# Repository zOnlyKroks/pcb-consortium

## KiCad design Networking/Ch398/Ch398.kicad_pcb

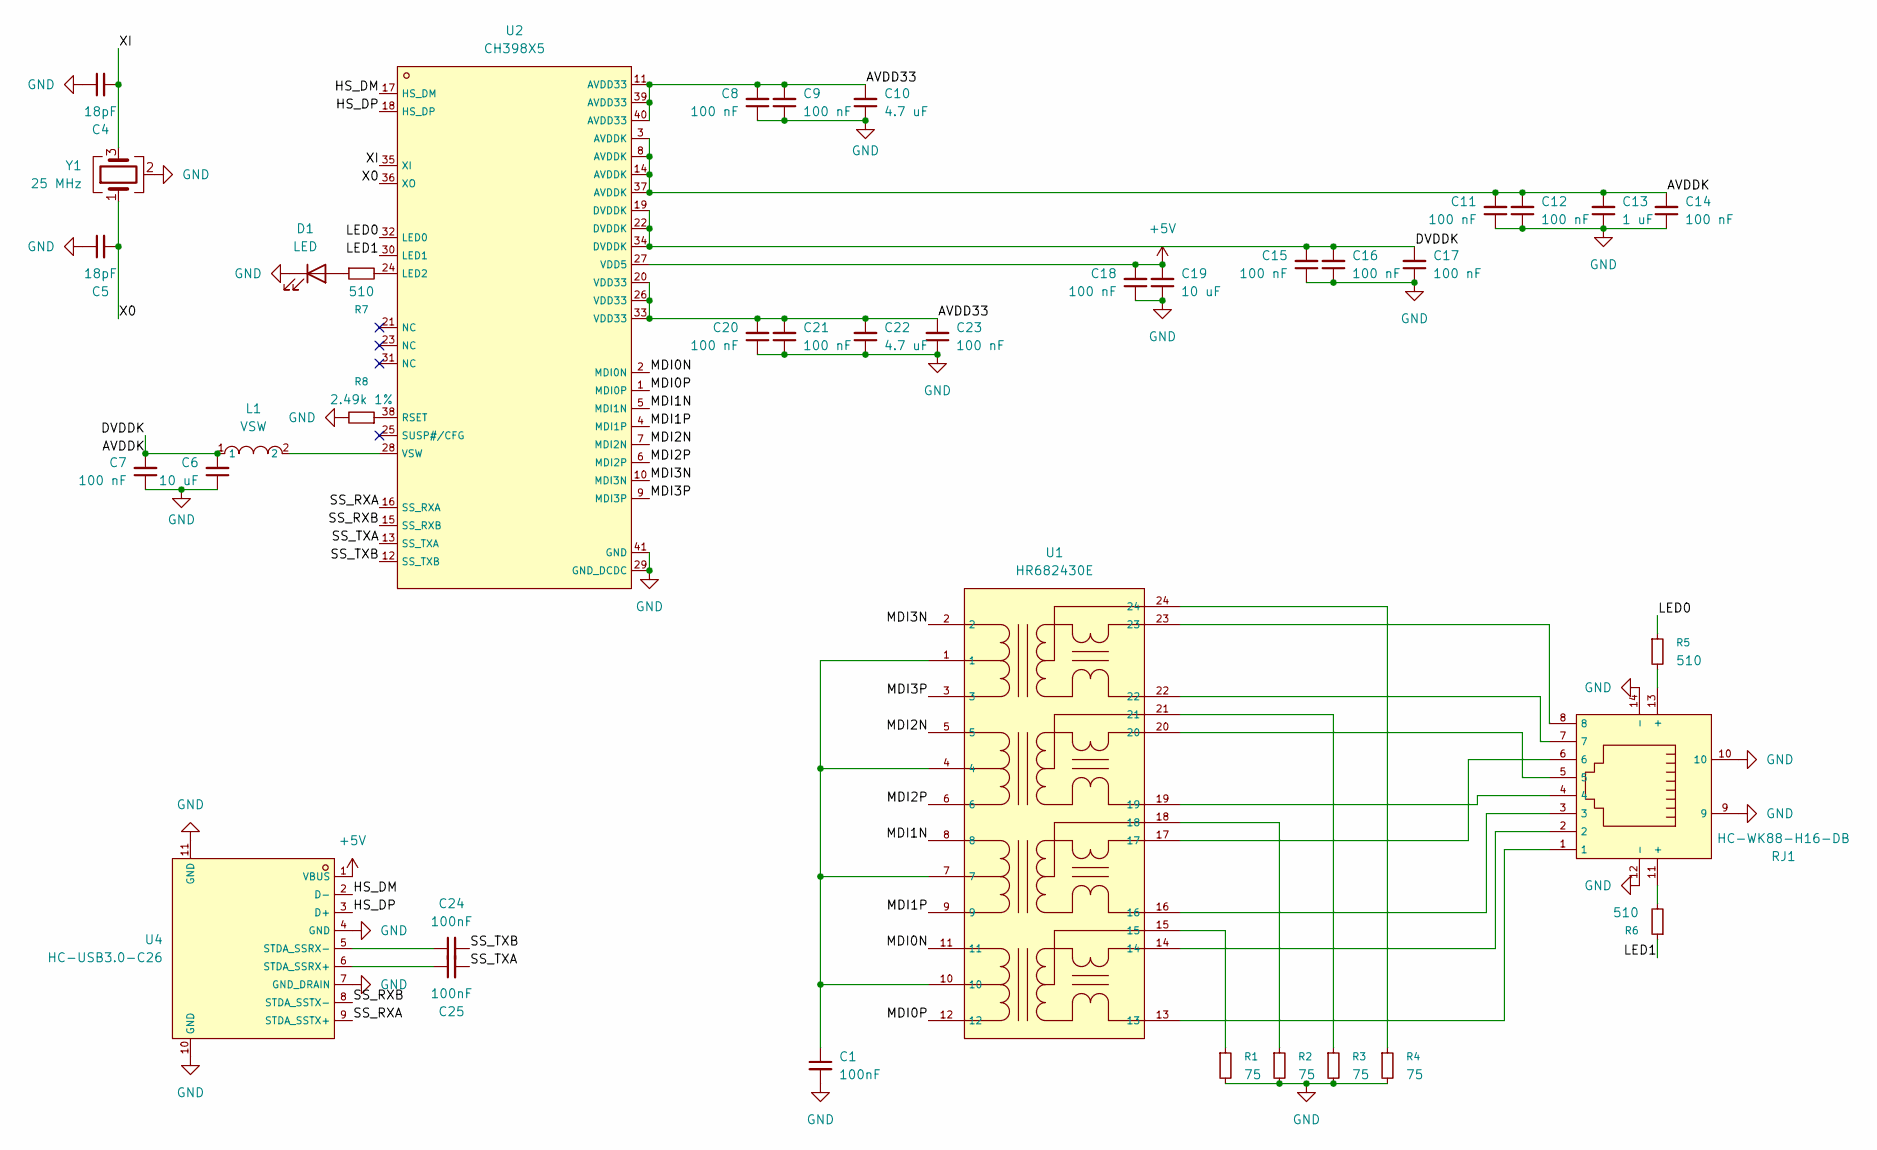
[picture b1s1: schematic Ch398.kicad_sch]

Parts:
C1, C24, C25: 100nF; C_0603_1608Metric
C4, C5: 18pF; C_0603_1608Metric
C6: 10 uF; C_0603_1608Metric
C7, C8, C9, C11, C12, C14, C15, C16, C17, C18, C20, C21, C23: 100 nF; C_0603_1608Metric
C10, C22: 4.7 uF; C_0805_2012Metric
C13: 1 uF; C_0603_1608Metric
C19: 10 uF; C_0805_2012Metric
D1: LED; LED_0805_2012Metric
L1: VSW; C47327201_IND-SMD_L7_7-W6_6_APS0630; LCSC C47327201
R1, R2, R3, R4: 75; R_0603_1608Metric
R5, R6, R7: 510; R_0603_1608Metric
R8: 2.49k 1%; R_0603_1608Metric
RJ1: HC-WK88-H16-DB; C7501824_RJ45-TH_HC-WK88-H16-DB; LCSC C7501824
U1: HR682430E; C3020103_SMD-24_L15_1-W7_1-P1_00-LS10_0-BL; LCSC C3020103
U2: CH398X5; C55013891_VQFN-40_L5_0-W5_0-P0_40-TL-EP3_5; LCSC C55013891
U4: HC-USB3.0-C26; C7501854_USB-3_0-A-SMD_HC-USB3_0-C26; LCSC C7501854
Y1: 25 MHz; Crystal_SMD_3225-4Pin_3.2x2.5mm

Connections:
+5V: C18.2, C19.2, U2.27 (VDD5), U4.1 (VBUS)
/AVDD33: C8.2, C9.2, C10.2, C20.2, C21.2, C22.2, C23.2, U2.11 (AVDD33), U2.20 (VDD33), U2.26 (VDD33), U2.33 (VDD33), U2.39 (AVDD33), U2.40 (AVDD33)
/AVDDK: C6.2, C7.2, C11.2, C12.2, C13.2, C14.2, C15.2, C16.2, C17.2, L1.1, U2.3 (AVDDK), U2.8 (AVDDK), U2.14 (AVDDK), U2.19 (DVDDK), U2.22 (DVDDK), U2.34 (DVDDK), U2.37 (AVDDK)
/HS_DM: U2.17 (HS_DM), U4.2 (D-)
/HS_DP: U2.18 (HS_DP), U4.3 (D+)
/LED0: R5.1, U2.32 (LED0)
/LED1: R6.1, U2.30 (LED1)
/MDI0N: U1.11, U2.2 (MDI0N)
/MDI0P: U1.12, U2.1 (MDI0P)
/MDI1N: U1.8, U2.5 (MDI1N)
/MDI1P: U1.9, U2.4 (MDI1P)
/MDI2N: U1.5, U2.7 (MDI2N)
/MDI2P: U1.6, U2.6 (MDI2P)
/MDI3N: U1.2, U2.10 (MDI3N)
/MDI3P: U1.3, U2.9 (MDI3P)
/SS_RXA: U2.16 (SS_RXA), U4.9 (STDA_SSTX+)
/SS_RXB: U2.15 (SS_RXB), U4.8 (STDA_SSTX-)
/SS_TXA: C25.2, U2.13 (SS_TXA)
/SS_TXB: C24.2, U2.12 (SS_TXB)
/X0: C5.2, U2.36 (XO), Y1.1
/XI: C4.2, U2.35 (XI), Y1.3
GND: C1.2, C4.1, C5.1, C6.1, C7.1, C8.1, C9.1, C10.1, C11.1, C12.1, C13.1, C14.1, C15.1, C16.1, C17.1, C18.1, C19.1, C20.1, C21.1, C22.1, C23.1, D1.1 (K), R1.2, R2.2, R3.2, R4.2, R8.2, RJ1.9, RJ1.10, RJ1.12 (-), RJ1.14 (-), U2.29 (GND_DCDC), U2.41 (GND), U4.4 (GND), U4.7 (GND_DRAIN), U4.10 (GND), U4.11 (GND), Y1.2 (G), Y1.4 (G)
unnamed: C1.1, U1.1, U1.4, U1.7, U1.10
unnamed: D1.2 (A), R7.1
unnamed: R1.1, U1.15
unnamed: R2.1, U1.18
unnamed: R3.1, U1.21
unnamed: R4.1, U1.24
unnamed: R5.2, RJ1.13 (+)
unnamed: R6.2, RJ1.11 (+)
unnamed: RJ1.1, U1.13
unnamed: RJ1.2, U1.14
unnamed: RJ1.3, U1.16
unnamed: RJ1.4, U1.19
unnamed: RJ1.5, U1.20
unnamed: RJ1.6, U1.17
unnamed: RJ1.7, U1.22
unnamed: RJ1.8, U1.23
unnamed: R7.2, U2.24 (LED2)
unnamed: R8.1, U2.38 (RSET)
unnamed: L1.2, U2.28 (VSW)
unnamed: C25.1, U4.6 (STDA_SSRX+)
unnamed: C24.1, U4.5 (STDA_SSRX-)

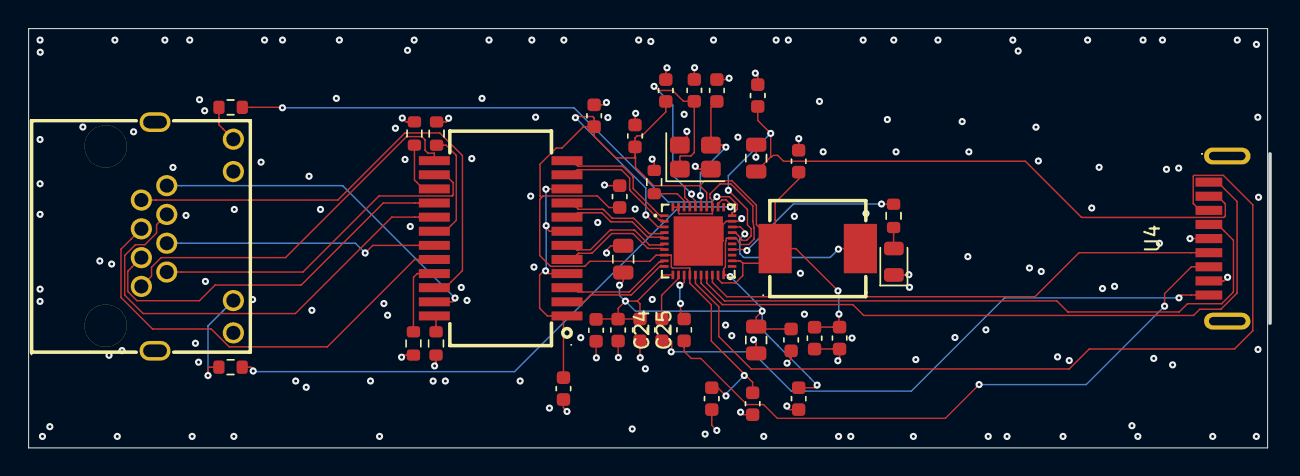
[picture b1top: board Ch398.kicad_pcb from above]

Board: 4 copper layers, 87.8 x 29.7 mm, 38 parts (0 on the bottom side), 43 nets.

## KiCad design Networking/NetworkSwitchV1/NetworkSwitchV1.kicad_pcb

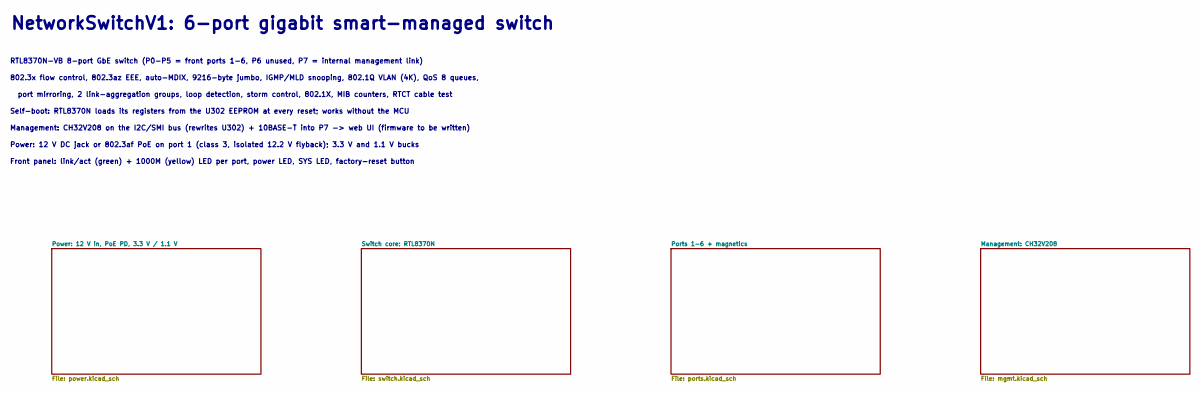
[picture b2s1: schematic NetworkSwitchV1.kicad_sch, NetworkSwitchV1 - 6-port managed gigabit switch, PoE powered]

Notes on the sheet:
Self-boot: RTL8370N loads its registers from the U302 EEPROM at every reset; works without the MCU
NetworkSwitchV1: 6-port gigabit smart-managed switch
802.3x flow control, 802.3az EEE, auto-MDIX, 9216-byte jumbo, IGMP/MLD snooping, 802.1Q VLAN (4K), QoS 8 queues,
Front panel: link/act (green) + 1000M (yellow) LED per port, power LED, SYS LED, factory-reset button
Power: 12 V DC jack or 802.3af PoE on port 1 (class 3, isolated 12.2 V flyback); 3.3 V and 1.1 V bucks
RTL8370N-VB 8-port GbE switch (P0-P5 = front ports 1-6, P6 unused, P7 = internal management link)
Management: CH32V208 on the I2C/SMI bus (rewrites U302) + 10BASE-T into P7 -> web UI (firmware to be written)
port mirroring, 2 link-aggregation groups, loop detection, storm control, 802.1X, MIB counters, RTCT cable test

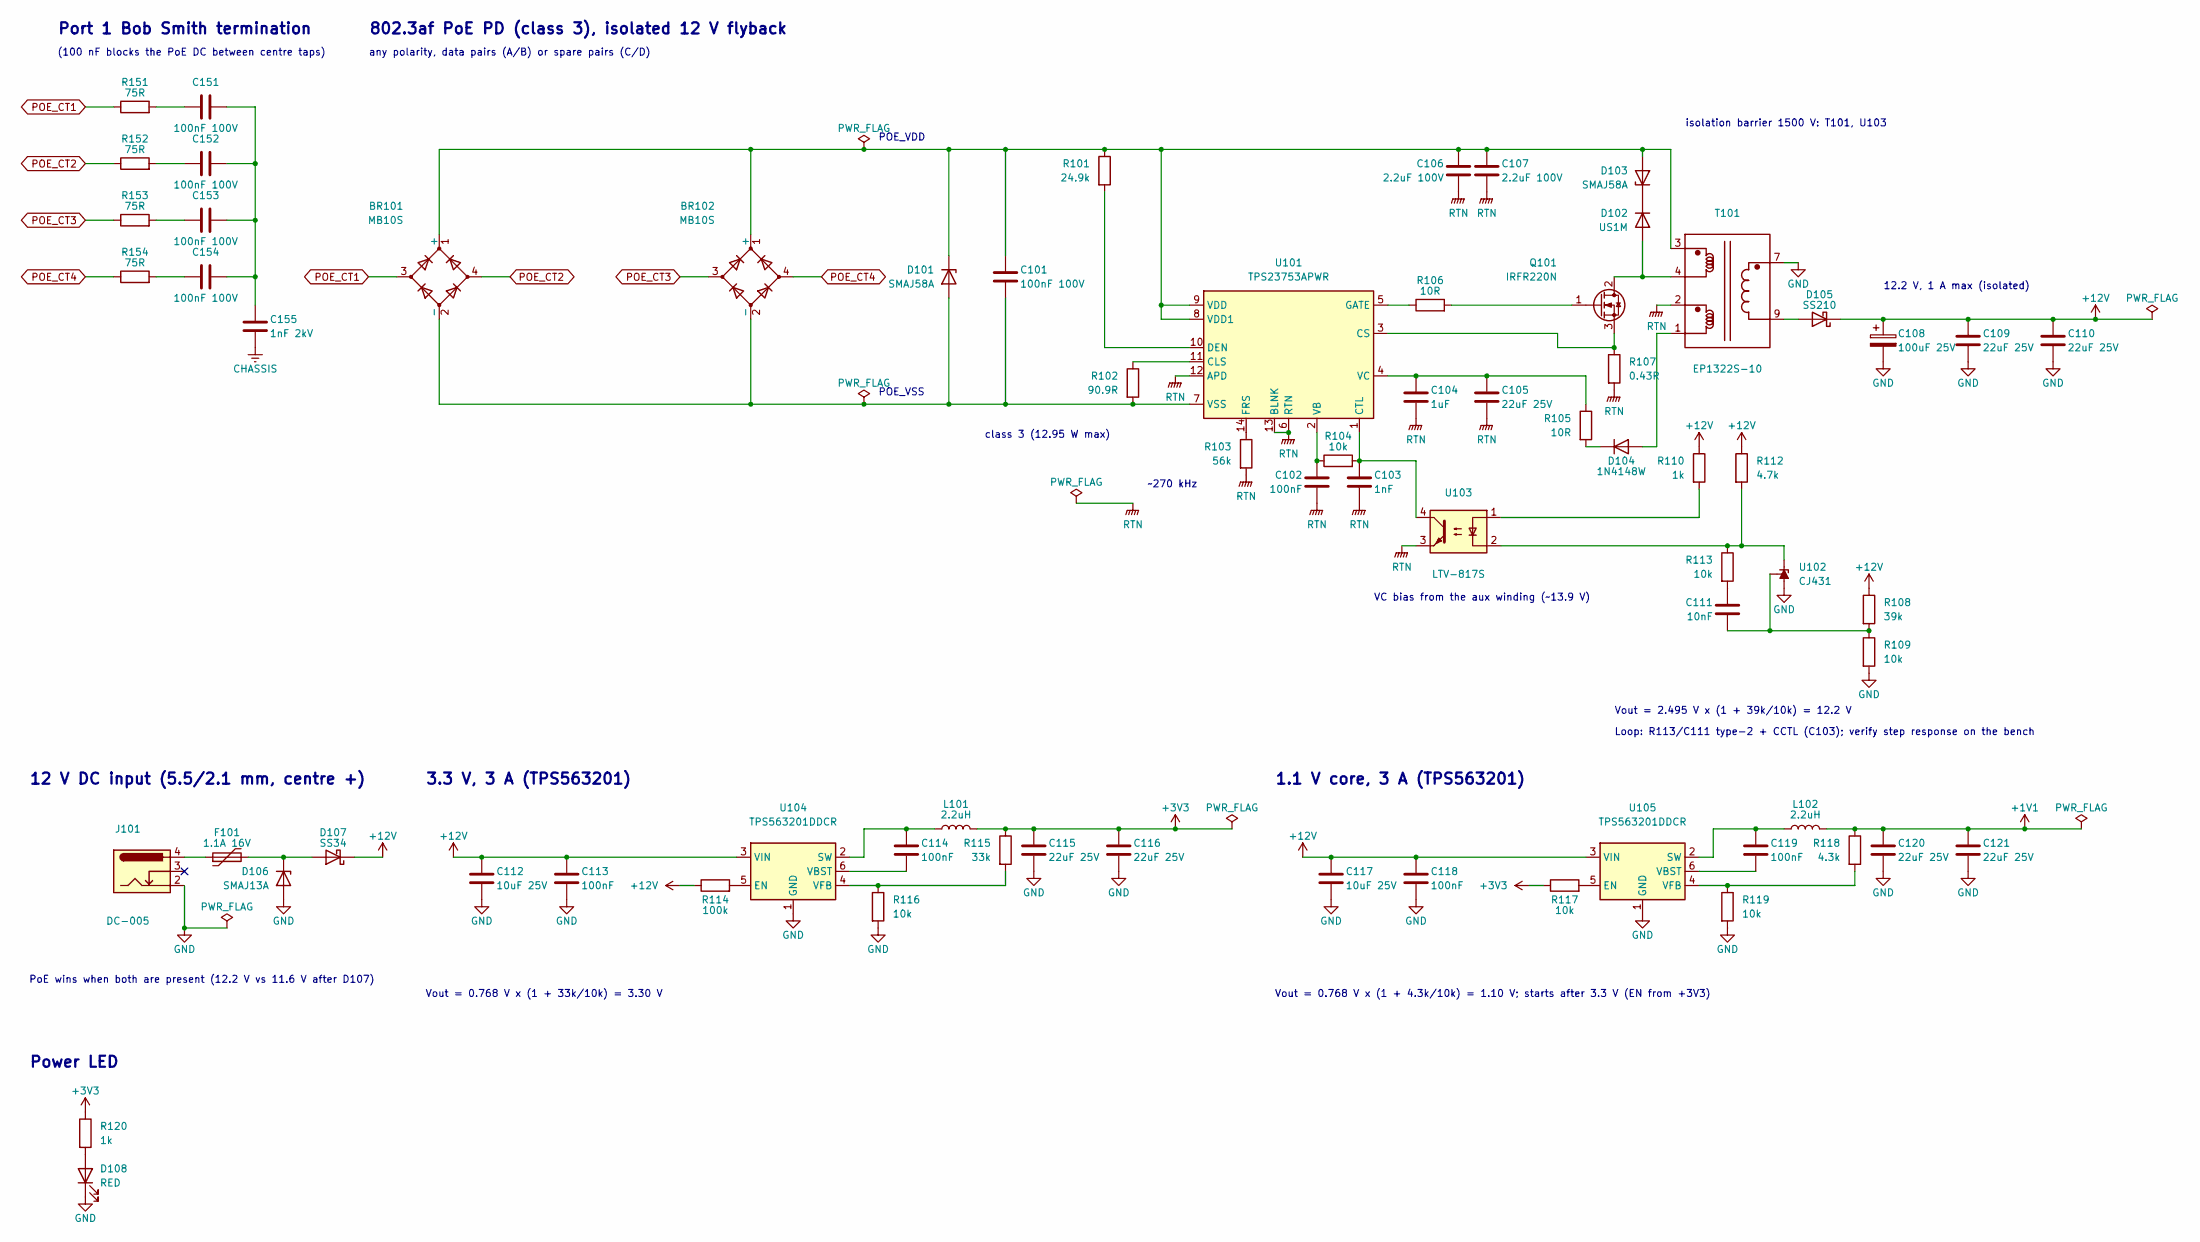
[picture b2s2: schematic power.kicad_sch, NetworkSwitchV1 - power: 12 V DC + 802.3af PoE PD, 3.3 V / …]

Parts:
BR101, BR102: MB10S; MBS_L4.7-W3.8-P2.40-LS7.0-TL; LCSC Part # C2488
C101, C151, C152, C153, C154: 100nF 100V; C_0805_2012Metric; LCSC Part # C28233
C102, C113, C114, C118, C119: 100nF; C_0603_1608Metric; LCSC Part # C14663
C103: 1nF; C_0603_1608Metric; LCSC Part # C1588
C104: 1uF; C_0603_1608Metric; LCSC Part # C15849
C105, C109, C110, C115, C116, C120, C121: 22uF 25V; C_0805_2012Metric; LCSC Part # C45783
C106, C107: 2.2uF 100V; C_1210_3225Metric; LCSC Part # C55151
C108: 100uF 25V; CP_Elec_6.3x7.7; LCSC Part # C970685
C111: 10nF; C_0603_1608Metric; LCSC Part # C57112
C112, C117: 10uF 25V; C_0805_2012Metric; LCSC Part # C15850
C155: 1nF 2kV; C_1206_3216Metric; LCSC Part # C9196
D101, D103: SMAJ58A; D_SMA; LCSC Part # C123816
D102: US1M; D_SMA; LCSC Part # C412437
D104: 1N4148W; D_SOD-123; LCSC Part # C81598
D105: SS210; D_SMA; LCSC Part # C14996
D106: SMAJ13A; D_SMA; LCSC Part # C10764
D107: SS34; D_SMA; LCSC Part # C8678
D108: RED; LED_0603_1608Metric; LCSC Part # C2286
F101: 1.1A 16V; Fuse_1206_3216Metric; LCSC Part # C7542961
J101: DC-005; DC-IN-TH_DC-005-5.5-2.0; LCSC Part # C16214
L101, L102: 2.2uH; IND-SMD_L4.0-W4.0_FNR40XXS; LCSC Part # C167869
Q101: IRFR220N; TO-252-2_L6.6-W6.1-P4.57-LS9.9-BR-CW; Rating 200 V 8 A; LCSC Part # C22365390
R101: 24.9k; R_0603_1608Metric; LCSC Part # C25962
R102: 90.9R; R_0603_1608Metric; LCSC Part # C23130
R103: 56k; R_0603_1608Metric; LCSC Part # C23206
R104, R109, R113, R116, R117, R119: 10k; R_0603_1608Metric; LCSC Part # C25804
R105, R106: 10R; R_0603_1608Metric; LCSC Part # C22859
R107: 0.43R; R_1206_3216Metric; LCSC Part # C24965
R108: 39k; R_0603_1608Metric; LCSC Part # C23153
R110, R120: 1k; R_0603_1608Metric; LCSC Part # C21190
R112: 4.7k; R_0603_1608Metric; LCSC Part # C23162
R114: 100k; R_0603_1608Metric; LCSC Part # C25803
R115: 33k; R_0603_1608Metric; LCSC Part # C4216
R118: 4.3k; R_0603_1608Metric; LCSC Part # C23159
R151, R152, R153, R154: 75R; R_0603_1608Metric; LCSC Part # C4275
T101: EP1322S-10; XFMR-SMD_EP1322S-10; LCSC Part # C37328796
U101: TPS23753APWR; TSSOP-14_L5.0-W4.4-P0.65-LS6.4-BL; LCSC Part # C92115
U102: CJ431; SOT-23-3_L2.9-W1.6-P1.90-LS2.8-BR; LCSC Part # C3113
U103: LTV-817S; OPTO-SMD-4_L4.6-W6.5-P2.54-LS10.3-BL; LCSC Part # C109227
U104, U105: TPS563201DDCR; TSOT-23-6; LCSC Part # C116592

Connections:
+1V1: C120.1, C121.1, L102.2, R118.1; also elsewhere on the board
+3V3: C115.1, C116.1, L101.2, R115.1, R117.1, R120.1; also elsewhere on the board
+12V: C108.1, C109.1, C110.1, C112.1, C113.1, C117.1, C118.1, D105.1 (K), D107.1 (K), R108.1, R110.1, R112.1, R114.1, U104.3 (VIN), U105.3 (VIN)
CHASSIS: C155.2; also elsewhere on the board
GND: C108.2, C109.2, C110.2, C112.2, C113.2, C115.2, C116.2, C117.2, C118.2, C120.2, C121.2, D106.2 (A), D108.1 (K), J101.2, R109.2, R116.2, R119.2, T101.7, T101.8, U102.3 (A), U104.1 (GND), U105.1 (GND); also elsewhere on the board
unnamed: BR101.1 (+), BR102.1 (+), C101.1, C106.1, C107.1, D101.1 (K), D103.2 (A), R101.1, T101.3, U101.8 (VDD1), U101.9 (VDD)
unnamed: BR101.2 (-), BR102.2 (-), C101.2, D101.2 (A), R102.2, U101.7 (VSS)
unnamed: C111.1, R113.2
unnamed: C151.1, R151.2
unnamed: C151.2, C152.2, C153.2, C154.2, C155.1
unnamed: C152.1, R152.2
unnamed: C153.1, R153.2
unnamed: C154.1, R154.2
unnamed: D102.2 (A), Q101.2 (D), T101.4
unnamed: D102.1 (K), D103.1 (K)
unnamed: D104.2 (A), T101.1
unnamed: D104.1 (K), R105.2
unnamed: D105.2 (A), T101.9, T101.10
unnamed: D106.1 (K), D107.2 (A), F101.2
unnamed: D108.2 (A), R120.2
unnamed: F101.1, J101.4
unnamed: Q101.1 (G), R106.2
unnamed: Q101.3 (S), R107.1, U101.3 (CS)
unnamed: R110.2, U103.1
unnamed: R102.1, U101.11 (CLS)
unnamed: C103.1, R104.2, U101.1 (CTL), U103.4
unnamed: R101.2, U101.10 (DEN)
unnamed: R103.1, U101.14 (FRS)
unnamed: R106.1, U101.5 (GATE)
unnamed: C102.1, R104.1, U101.2 (VB)
unnamed: C104.1, C105.1, R105.1, U101.4 (VC)
unnamed: R112.2, R113.1, U102.2 (K), U103.2
unnamed: C111.2, R108.2, R109.1, U102.1 (REF)
unnamed: R114.2, U104.5 (EN)
unnamed: C114.1, L101.1, U104.2 (SW)
unnamed: C114.2, U104.6 (VBST)
unnamed: R115.2, R116.1, U104.4 (VFB)
unnamed: R117.2, U105.5 (EN)
unnamed: C119.1, L102.1, U105.2 (SW)
unnamed: C119.2, U105.6 (VBST)
unnamed: R118.2, R119.1, U105.4 (VFB)
POE_CT1: BR101.3, R151.1; also elsewhere on the board
POE_CT2: BR101.4, R152.1; also elsewhere on the board
POE_CT3: BR102.3, R153.1; also elsewhere on the board
POE_CT4: BR102.4, R154.1; also elsewhere on the board
RTN: C102.2, C103.2, C104.2, C105.2, C106.2, C107.2, R103.2, R107.2, T101.2, U101.6 (RTN), U101.12 (APD), U101.13 (BLNK), U103.3

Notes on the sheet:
any polarity, data pairs (A/B) or spare pairs (C/D)
3.3 V, 3 A (TPS563201)
Vout = 2.495 V x (1 + 39k/10k) = 12.2 V
~270 kHz
class 3 (12.95 W max)
Port 1 Bob Smith termination
Loop: R113/C111 type-2 + CCTL (C103); verify step response on the bench
802.3af PoE PD (class 3), isolated 12 V flyback
POE_VDD
VC bias from the aux winding (~13.9 V)
1.1 V core, 3 A (TPS563201)
12.2 V, 1 A max (isolated)
Vout = 0.768 V x (1 + 33k/10k) = 3.30 V
POE_VSS
Vout = 0.768 V x (1 + 4.3k/10k) = 1.10 V; starts after 3.3 V (EN from +3V3)
isolation barrier 1500 V: T101, U103
(100 nF blocks the PoE DC between centre taps)
Power LED
12 V DC input (5.5/2.1 mm, centre +)
PoE wins when both are present (12.2 V vs 11.6 V after D107)

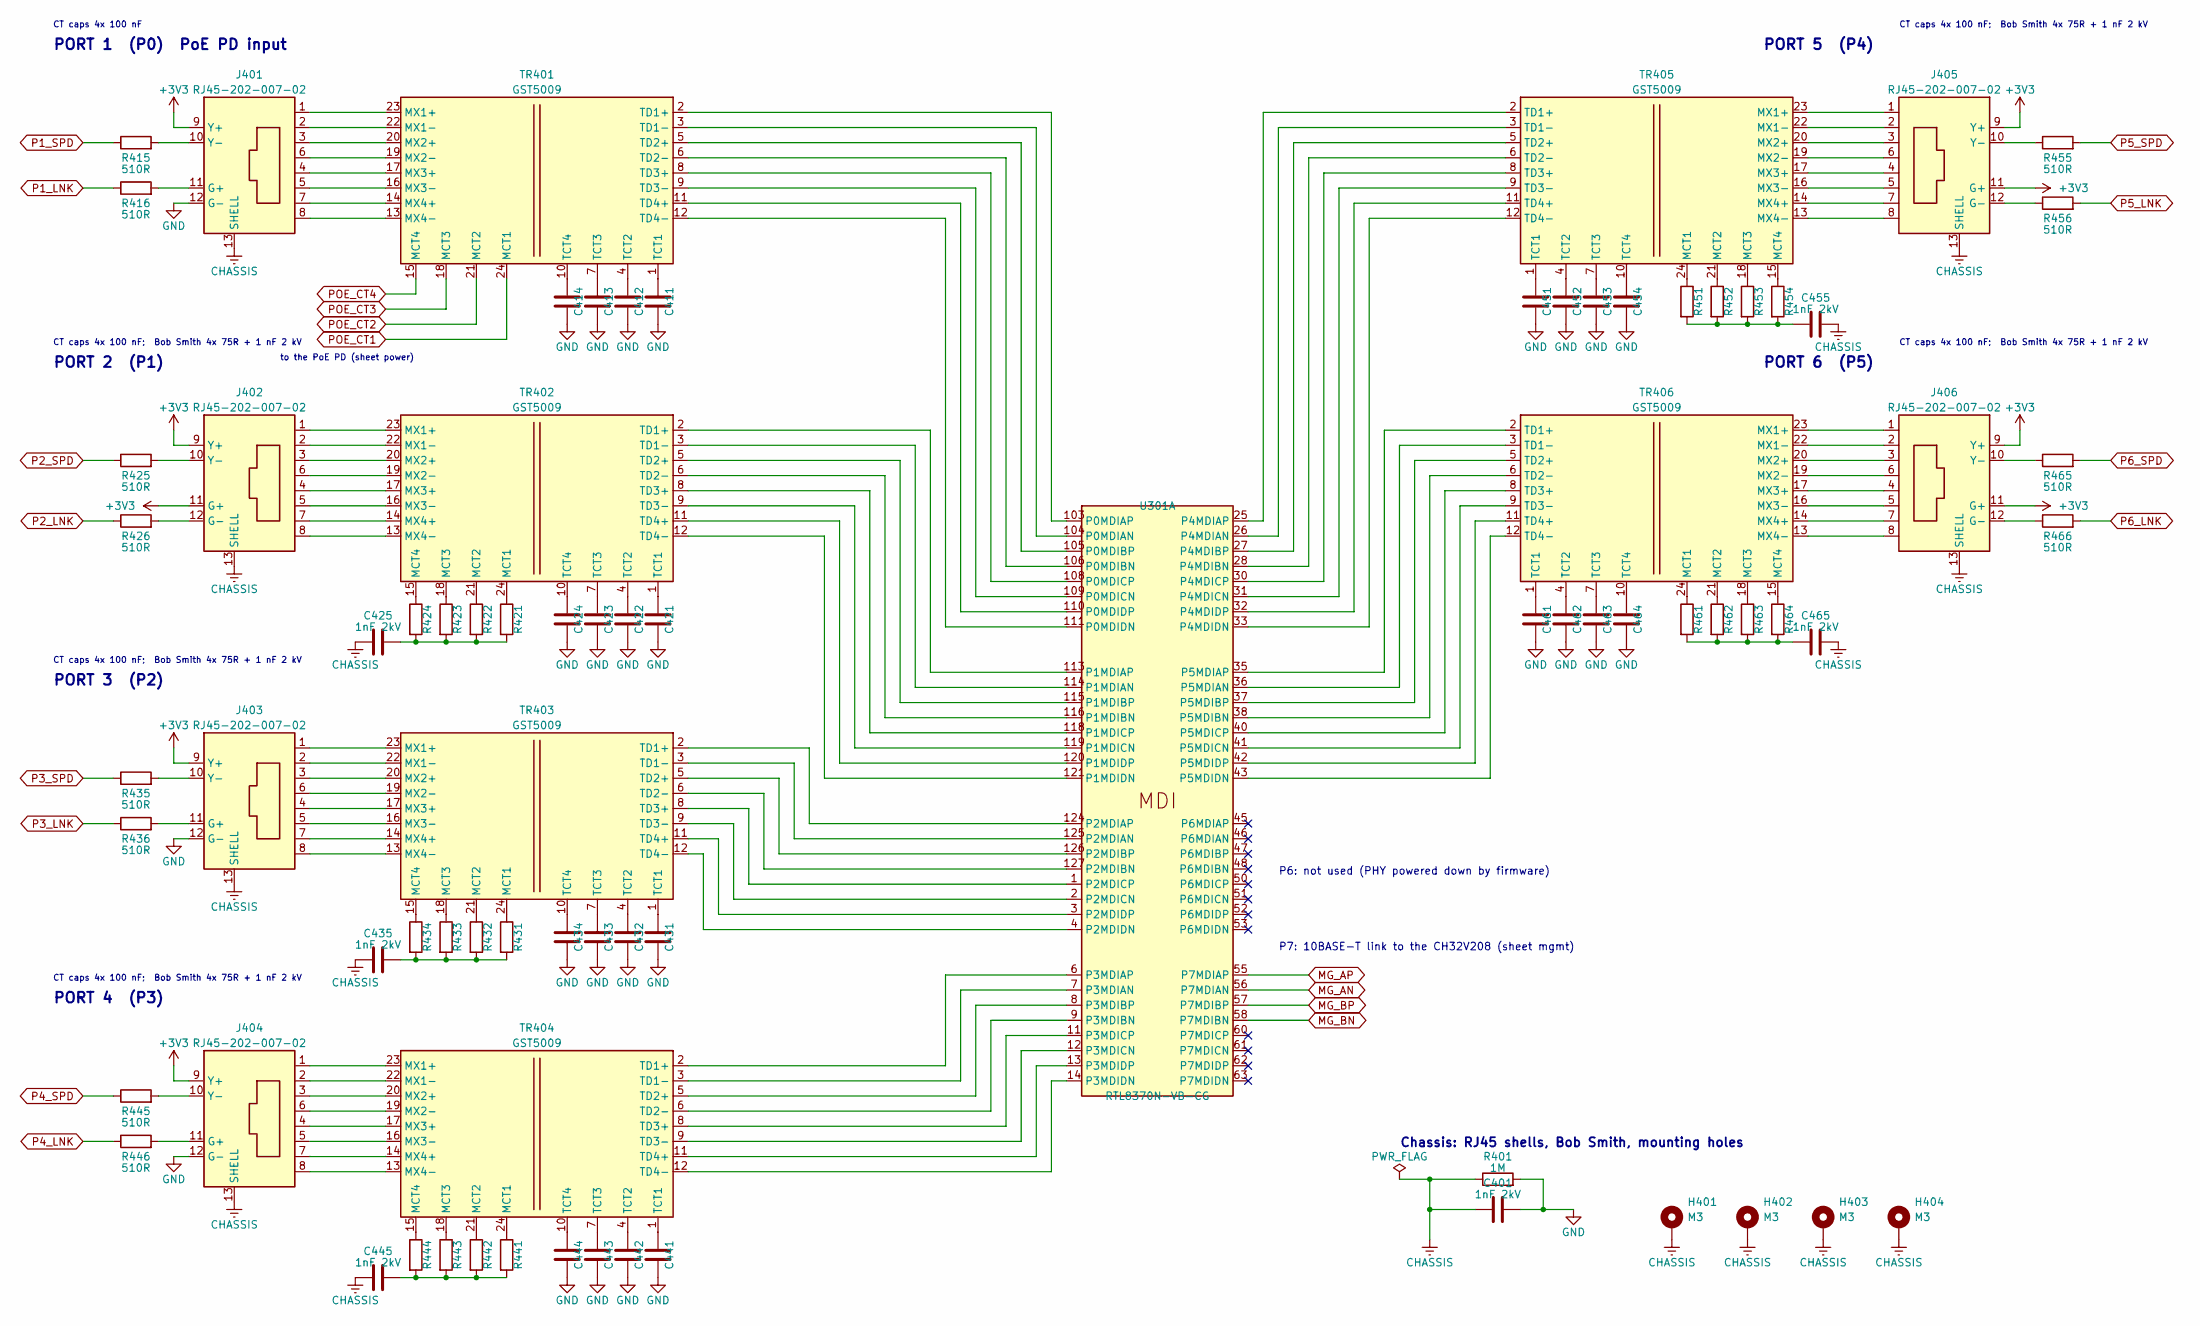
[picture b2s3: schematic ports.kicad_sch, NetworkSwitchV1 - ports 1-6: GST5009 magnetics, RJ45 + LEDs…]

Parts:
C401, C425, C435, C445, C455, C465: 1nF 2kV; C_1206_3216Metric; LCSC Part # C9196
C411, C412, C413, C414, C421, C422, C423, C424, C431, C432, C433, C434, C441, C442, C443, C444, C451, C452, C453, C454, C461, C462, C463, C464: 100nF; C_0603_1608Metric; LCSC Part # C14663
H401, H402, H403, H404: M3; MountingHole_3.2mm_M3_Pad_Via
J401, J402, J403, J404, J405, J406: RJ45-202-007-02; RJ45-TH_RJ45-202-007-02; LCSC Part # C7421418
R401: 1M; R_0603_1608Metric; LCSC Part # C22935
R415, R416, R425, R426, R435, R436, R445, R446, R455, R456, R465, R466: 510R; R_0603_1608Metric; LCSC Part # C23193
R421, R422, R423, R424, R431, R432, R433, R434, R441, R442, R443, R444, R451, R452, R453, R454, R461, R462, R463, R464: 75R; R_0603_1608Metric; LCSC Part # C4275
TR401, TR402, TR403, TR404, TR405, TR406: GST5009; XFMR-SMD_24P-L15.1-W7.1-P1.00-LS9.7-BL; LCSC Part # C55213474
U301: RTL8370N-VB-CG; LQFP-128_L20.0-W14.0-P0.50-BL-EP7.0; LCSC Part # C2803243

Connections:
+3V3: J401.9 (Y+), J402.9 (Y+), J402.11 (G+), J403.9 (Y+), J404.9 (Y+), J405.9 (Y+), J405.11 (G+), J406.9 (Y+), J406.11 (G+); also elsewhere on the board
CHASSIS: C401.1, C425.1, C435.1, C445.1, C455.2, C465.2, H401.1 (1_1), H402.1 (1_1), H403.1 (1_1), H404.1 (1_1), J401.13 (SHELL), J402.13 (SHELL), J403.13 (SHELL), J404.13 (SHELL), J405.13 (SHELL), J406.13 (SHELL), R401.1; also elsewhere on the board
GND: C401.2, C411.2, C412.2, C413.2, C414.2, C421.2, C422.2, C423.2, C424.2, C431.2, C432.2, C433.2, C434.2, C441.2, C442.2, C443.2, C444.2, C451.2, C452.2, C453.2, C454.2, C461.2, C462.2, C463.2, C464.2, J401.12 (G-), J403.12 (G-), J404.12 (G-), R401.2; also elsewhere on the board
MG_AN: U301.56 (P7MDIAN); also elsewhere on the board
MG_AP: U301.55 (P7MDIAP); also elsewhere on the board
MG_BN: U301.58 (P7MDIBN); also elsewhere on the board
MG_BP: U301.57 (P7MDIBP); also elsewhere on the board
unnamed: C425.2, R421.2, R422.2, R423.2, R424.2
unnamed: C435.2, R431.2, R432.2, R433.2, R434.2
unnamed: C445.2, R441.2, R442.2, R443.2, R444.2
unnamed: C455.1, R451.2, R452.2, R453.2, R454.2
unnamed: C465.1, R461.2, R462.2, R463.2, R464.2
unnamed: J401.11 (G+), R416.2
unnamed: J401.10 (Y-), R415.2
unnamed: J402.12 (G-), R426.2
unnamed: J402.10 (Y-), R425.2
unnamed: J403.11 (G+), R436.2
unnamed: J403.10 (Y-), R435.2
unnamed: J404.11 (G+), R446.2
unnamed: J404.10 (Y-), R445.2
unnamed: J405.12 (G-), R456.1
unnamed: J405.10 (Y-), R455.1
unnamed: J406.12 (G-), R466.1
unnamed: J406.10 (Y-), R465.1
unnamed: J401.1, TR401.23 (MX1+)
unnamed: J401.2, TR401.22 (MX1-)
unnamed: J401.3, TR401.20 (MX2+)
unnamed: J401.6, TR401.19 (MX2-)
unnamed: J401.4, TR401.17 (MX3+)
unnamed: J401.5, TR401.16 (MX3-)
unnamed: J401.7, TR401.14 (MX4+)
unnamed: J401.8, TR401.13 (MX4-)
unnamed: C411.1, TR401.1 (TCT1)
unnamed: C412.1, TR401.4 (TCT2)
unnamed: C413.1, TR401.7 (TCT3)
unnamed: C414.1, TR401.10 (TCT4)
unnamed: TR401.2 (TD1+), U301.103 (P0MDIAP)
unnamed: TR401.3 (TD1-), U301.104 (P0MDIAN)
unnamed: TR401.5 (TD2+), U301.105 (P0MDIBP)
unnamed: TR401.6 (TD2-), U301.106 (P0MDIBN)
unnamed: TR401.8 (TD3+), U301.108 (P0MDICP)
unnamed: TR401.9 (TD3-), U301.109 (P0MDICN)
unnamed: TR401.11 (TD4+), U301.110 (P0MDIDP)
unnamed: TR401.12 (TD4-), U301.111 (P0MDIDN)
unnamed: R421.1, TR402.24 (MCT1)
unnamed: R422.1, TR402.21 (MCT2)
unnamed: R423.1, TR402.18 (MCT3)
unnamed: R424.1, TR402.15 (MCT4)
unnamed: J402.1, TR402.23 (MX1+)
unnamed: J402.2, TR402.22 (MX1-)
unnamed: J402.3, TR402.20 (MX2+)
unnamed: J402.6, TR402.19 (MX2-)
unnamed: J402.4, TR402.17 (MX3+)
unnamed: J402.5, TR402.16 (MX3-)
unnamed: J402.7, TR402.14 (MX4+)
unnamed: J402.8, TR402.13 (MX4-)
unnamed: C421.1, TR402.1 (TCT1)
unnamed: C422.1, TR402.4 (TCT2)
unnamed: C423.1, TR402.7 (TCT3)
unnamed: C424.1, TR402.10 (TCT4)
unnamed: TR402.2 (TD1+), U301.113 (P1MDIAP)
unnamed: TR402.3 (TD1-), U301.114 (P1MDIAN)
unnamed: TR402.5 (TD2+), U301.115 (P1MDIBP)
unnamed: TR402.6 (TD2-), U301.116 (P1MDIBN)
unnamed: TR402.8 (TD3+), U301.118 (P1MDICP)
unnamed: TR402.9 (TD3-), U301.119 (P1MDICN)
unnamed: TR402.11 (TD4+), U301.120 (P1MDIDP)
unnamed: TR402.12 (TD4-), U301.121 (P1MDIDN)
unnamed: R431.1, TR403.24 (MCT1)
unnamed: R432.1, TR403.21 (MCT2)
unnamed: R433.1, TR403.18 (MCT3)
unnamed: R434.1, TR403.15 (MCT4)
unnamed: J403.1, TR403.23 (MX1+)
unnamed: J403.2, TR403.22 (MX1-)
unnamed: J403.3, TR403.20 (MX2+)
unnamed: J403.6, TR403.19 (MX2-)
unnamed: J403.4, TR403.17 (MX3+)
unnamed: J403.5, TR403.16 (MX3-)
unnamed: J403.7, TR403.14 (MX4+)
unnamed: J403.8, TR403.13 (MX4-)
unnamed: C431.1, TR403.1 (TCT1)
unnamed: C432.1, TR403.4 (TCT2)
unnamed: C433.1, TR403.7 (TCT3)
unnamed: C434.1, TR403.10 (TCT4)
unnamed: TR403.2 (TD1+), U301.124 (P2MDIAP)
unnamed: TR403.3 (TD1-), U301.125 (P2MDIAN)
unnamed: TR403.5 (TD2+), U301.126 (P2MDIBP)
unnamed: TR403.6 (TD2-), U301.127 (P2MDIBN)
unnamed: TR403.8 (TD3+), U301.1 (P2MDICP)
unnamed: TR403.9 (TD3-), U301.2 (P2MDICN)
unnamed: TR403.11 (TD4+), U301.3 (P2MDIDP)
unnamed: TR403.12 (TD4-), U301.4 (P2MDIDN)
unnamed: R441.1, TR404.24 (MCT1)
unnamed: R442.1, TR404.21 (MCT2)
unnamed: R443.1, TR404.18 (MCT3)
unnamed: R444.1, TR404.15 (MCT4)
unnamed: J404.1, TR404.23 (MX1+)
unnamed: J404.2, TR404.22 (MX1-)
unnamed: J404.3, TR404.20 (MX2+)
unnamed: J404.6, TR404.19 (MX2-)
unnamed: J404.4, TR404.17 (MX3+)
unnamed: J404.5, TR404.16 (MX3-)
unnamed: J404.7, TR404.14 (MX4+)
unnamed: J404.8, TR404.13 (MX4-)
unnamed: C441.1, TR404.1 (TCT1)
unnamed: C442.1, TR404.4 (TCT2)
unnamed: C443.1, TR404.7 (TCT3)
unnamed: C444.1, TR404.10 (TCT4)
unnamed: TR404.2 (TD1+), U301.6 (P3MDIAP)
unnamed: TR404.3 (TD1-), U301.7 (P3MDIAN)
unnamed: TR404.5 (TD2+), U301.8 (P3MDIBP)
unnamed: TR404.6 (TD2-), U301.9 (P3MDIBN)
unnamed: TR404.8 (TD3+), U301.11 (P3MDICP)
unnamed: TR404.9 (TD3-), U301.12 (P3MDICN)
unnamed: TR404.11 (TD4+), U301.13 (P3MDIDP)
unnamed: TR404.12 (TD4-), U301.14 (P3MDIDN)
unnamed: R451.1, TR405.24 (MCT1)
unnamed: R452.1, TR405.21 (MCT2)
unnamed: R453.1, TR405.18 (MCT3)
unnamed: R454.1, TR405.15 (MCT4)
unnamed: J405.1, TR405.23 (MX1+)
unnamed: J405.2, TR405.22 (MX1-)
unnamed: J405.3, TR405.20 (MX2+)
unnamed: J405.6, TR405.19 (MX2-)
unnamed: J405.4, TR405.17 (MX3+)
unnamed: J405.5, TR405.16 (MX3-)
unnamed: J405.7, TR405.14 (MX4+)
unnamed: J405.8, TR405.13 (MX4-)
unnamed: C451.1, TR405.1 (TCT1)
unnamed: C452.1, TR405.4 (TCT2)
unnamed: C453.1, TR405.7 (TCT3)
unnamed: C454.1, TR405.10 (TCT4)
unnamed: TR405.2 (TD1+), U301.25 (P4MDIAP)
unnamed: TR405.3 (TD1-), U301.26 (P4MDIAN)
unnamed: TR405.5 (TD2+), U301.27 (P4MDIBP)
unnamed: TR405.6 (TD2-), U301.28 (P4MDIBN)
unnamed: TR405.8 (TD3+), U301.30 (P4MDICP)
unnamed: TR405.9 (TD3-), U301.31 (P4MDICN)
unnamed: TR405.11 (TD4+), U301.32 (P4MDIDP)
unnamed: TR405.12 (TD4-), U301.33 (P4MDIDN)
unnamed: R461.1, TR406.24 (MCT1)
unnamed: R462.1, TR406.21 (MCT2)
unnamed: R463.1, TR406.18 (MCT3)
unnamed: R464.1, TR406.15 (MCT4)
unnamed: J406.1, TR406.23 (MX1+)
unnamed: J406.2, TR406.22 (MX1-)
unnamed: J406.3, TR406.20 (MX2+)
unnamed: J406.6, TR406.19 (MX2-)
unnamed: J406.4, TR406.17 (MX3+)
unnamed: J406.5, TR406.16 (MX3-)
unnamed: J406.7, TR406.14 (MX4+)
unnamed: J406.8, TR406.13 (MX4-)
unnamed: C461.1, TR406.1 (TCT1)
unnamed: C462.1, TR406.4 (TCT2)
unnamed: C463.1, TR406.7 (TCT3)
unnamed: C464.1, TR406.10 (TCT4)
unnamed: TR406.2 (TD1+), U301.35 (P5MDIAP)
unnamed: TR406.3 (TD1-), U301.36 (P5MDIAN)
unnamed: TR406.5 (TD2+), U301.37 (P5MDIBP)
unnamed: TR406.6 (TD2-), U301.38 (P5MDIBN)
unnamed: TR406.8 (TD3+), U301.40 (P5MDICP)
unnamed: TR406.9 (TD3-), U301.41 (P5MDICN)
unnamed: TR406.11 (TD4+), U301.42 (P5MDIDP)
unnamed: TR406.12 (TD4-), U301.43 (P5MDIDN)
P1_LNK: R416.1; also elsewhere on the board
P1_SPD: R415.1; also elsewhere on the board
P2_LNK: R426.1; also elsewhere on the board
P2_SPD: R425.1; also elsewhere on the board
P3_LNK: R436.1; also elsewhere on the board
P3_SPD: R435.1; also elsewhere on the board
P4_LNK: R446.1; also elsewhere on the board
P4_SPD: R445.1; also elsewhere on the board
P5_LNK: R456.2; also elsewhere on the board
P5_SPD: R455.2; also elsewhere on the board
P6_LNK: R466.2; also elsewhere on the board
P6_SPD: R465.2; also elsewhere on the board
POE_CT1: TR401.24 (MCT1); also elsewhere on the board
POE_CT2: TR401.21 (MCT2); also elsewhere on the board
POE_CT3: TR401.18 (MCT3); also elsewhere on the board
POE_CT4: TR401.15 (MCT4); also elsewhere on the board

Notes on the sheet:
PORT 4 (P3)
CT caps 4x 100 nF; Bob Smith 4x 75R + 1 nF 2 kV
PORT 3 (P2)
CT caps 4x 100 nF
PORT 1 (P0) PoE PD input
PORT 2 (P1)
Chassis: RJ45 shells, Bob Smith, mounting holes
to the PoE PD (sheet power)
PORT 6 (P5)
P6: not used (PHY powered down by firmware)
P7: 10BASE-T link to the CH32V208 (sheet mgmt)
PORT 5 (P4)
